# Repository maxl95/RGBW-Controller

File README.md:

# RGBW-Controller
This is a low cost and tasmota compatile RGBW-Controller as an alternative to MagicHome devices.
Everything is untested until now.

# Some specs:
- operating voltage 12V (becaus of the mini360)
- max current per channel (color) 5A in theory 
- fully compatible with [Tasmota](https://github.com/arendst/Tasmota)
- price/piece around 5.60€
- dimensions 20mm x 35mm

# Tasmota template:

# known bugs:
- ~Short circuit between +12V and GND because of a polygon error~

# Pictures:

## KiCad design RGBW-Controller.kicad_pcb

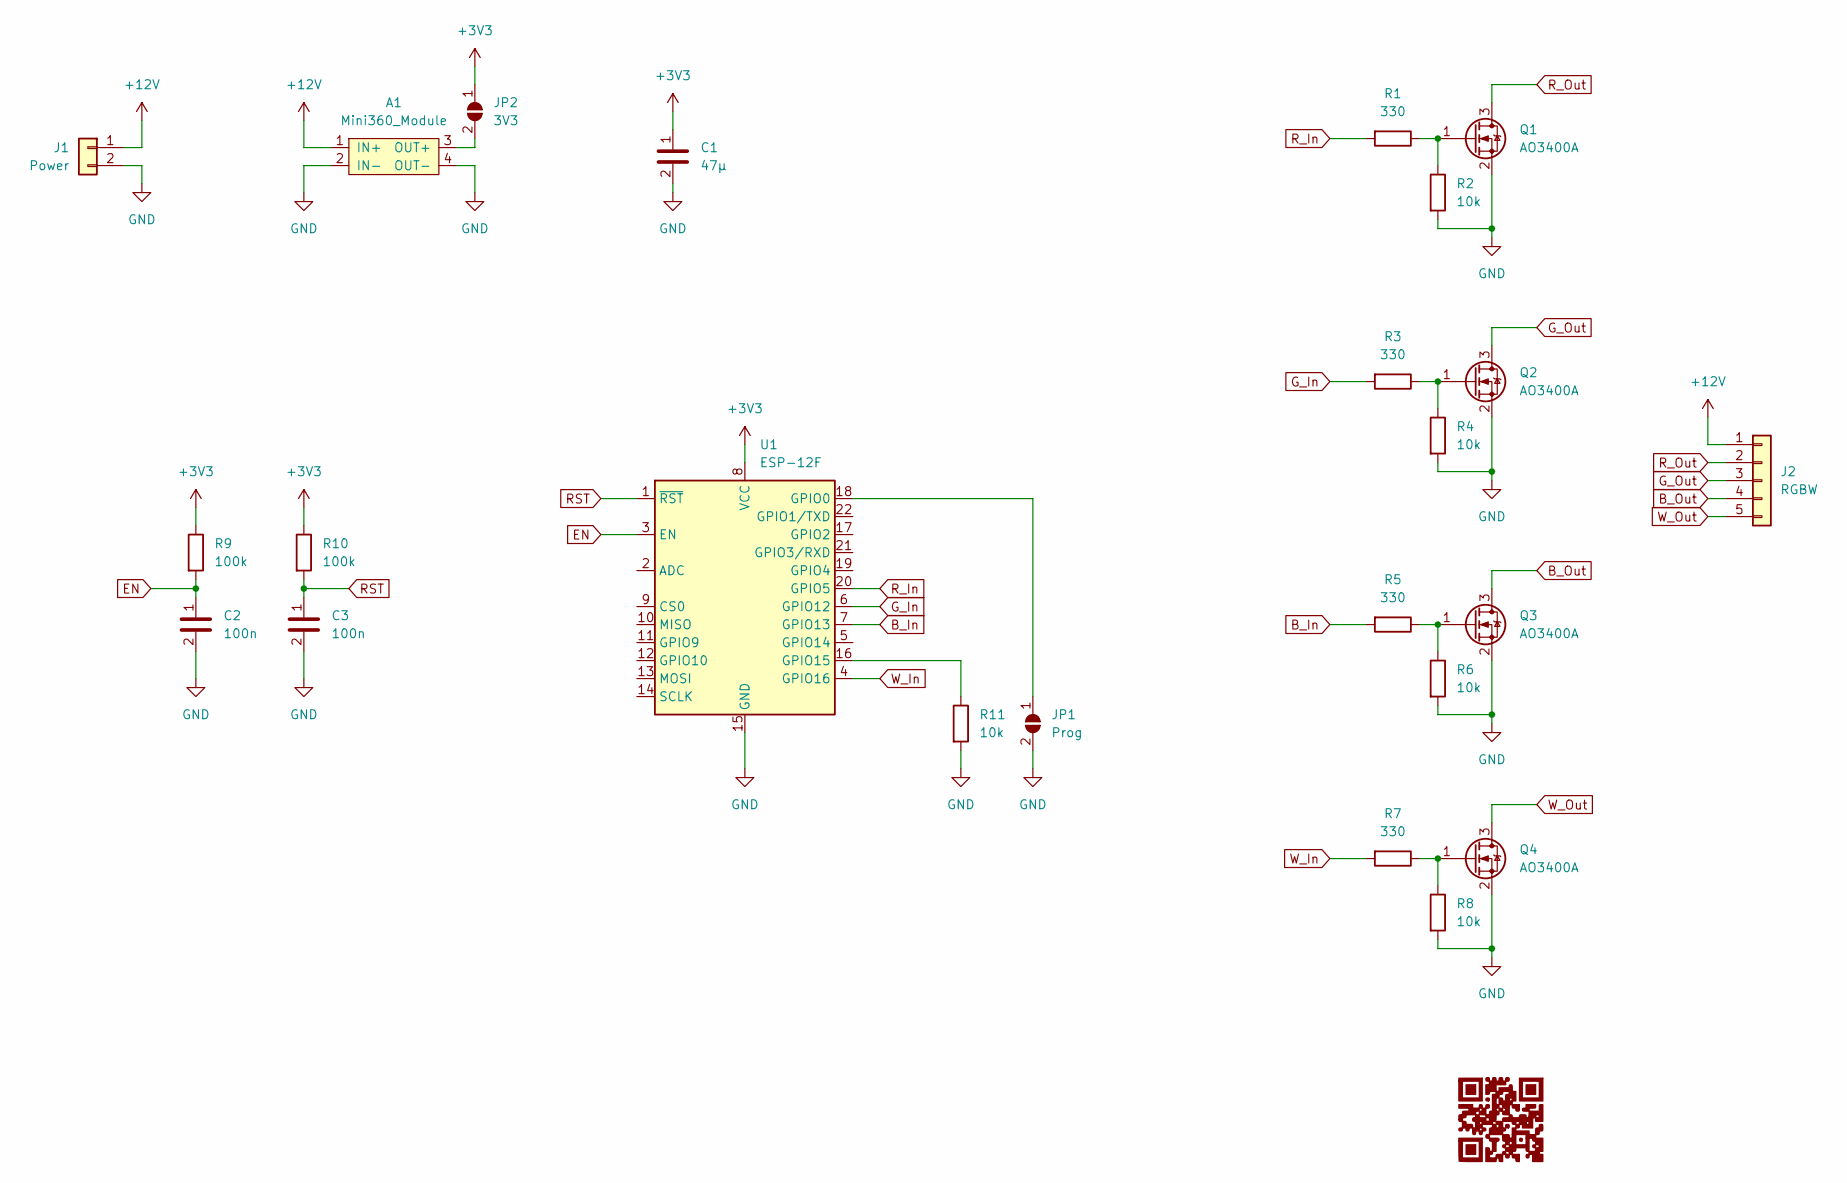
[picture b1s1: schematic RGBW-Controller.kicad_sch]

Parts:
A1: Mini360_Module
C1: 47µ; CP_EIA-3528-12_Kemet-T_Pad1.50x2.35mm_HandSolder
C2, C3: 100n; C_0805_2012Metric_Pad1.18x1.45mm_HandSolder
J1: Power; PinHeader_1x02_P2.54mm_Vertical
J2: RGBW; PinHeader_1x05_P2.54mm_Horizontal
JP1: Prog; SolderJumper-2_P1.3mm_Open_Pad1.0x1.5mm
JP2: 3V3; SolderJumper-2_P1.3mm_Open_Pad1.0x1.5mm
Q1, Q2, Q3, Q4: AO3400A; SOT-23
R1, R3, R5, R7: 330; R_0603_1608Metric
R2, R4, R6, R8: 10k; R_0603_1608Metric
R9, R10: 100k; R_0603_1608Metric_Pad0.98x0.95mm_HandSolder
R11: 10k; R_0603_1608Metric_Pad0.98x0.95mm_HandSolder
U1: ESP-12F; ESP-12E

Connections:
+3V3: C1.1, JP2.1 (A), R9.1, R10.1, U1.8 (VCC)
+12V: A1.1 (IN+), J1.1, J2.1; also elsewhere on the board
B_In: R5.2, U1.7 (GPIO13)
B_Out: J2.4, Q3.3 (D)
EN: C2.1, R9.2, U1.3 (EN)
GND: A1.2 (IN-), A1.4 (OUT-), C1.2, C2.2, C3.2, J1.2, JP1.2 (B), Q1.2 (S), Q2.2 (S), Q3.2 (S), Q4.2 (S), R2.2, R4.2, R6.2, R8.2, R11.2, U1.15 (GND); also elsewhere on the board
G_In: R3.2, U1.6 (GPIO12)
G_Out: J2.3, Q2.3 (D)
unnamed: A1.3 (OUT+), JP2.2 (B)
unnamed: JP1.1 (A), U1.18 (GPIO0)
unnamed: Q1.1 (G), R1.1, R2.1
unnamed: Q2.1 (G), R3.1, R4.1
unnamed: Q3.1 (G), R5.1, R6.1
unnamed: Q4.1 (G), R7.1, R8.1
unnamed: R11.1, U1.16 (GPIO15)
RST: C3.1, R10.2, U1.1 (~RST)
R_In: R1.2, U1.20 (GPIO5)
R_Out: J2.2, Q1.3 (D)
W_In: R7.2, U1.4 (GPIO16)
W_Out: J2.5, Q4.3 (D)

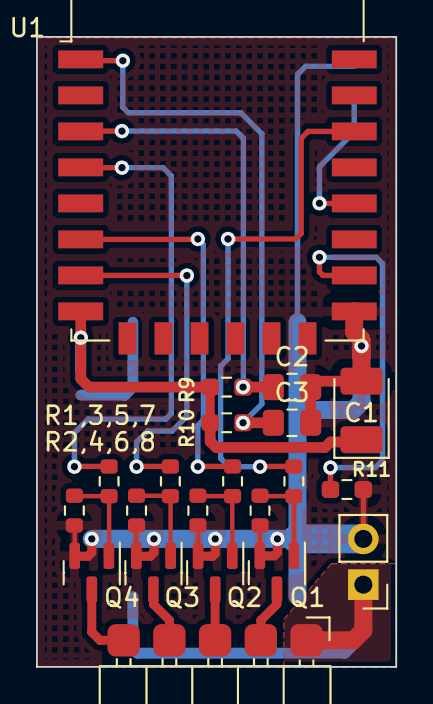
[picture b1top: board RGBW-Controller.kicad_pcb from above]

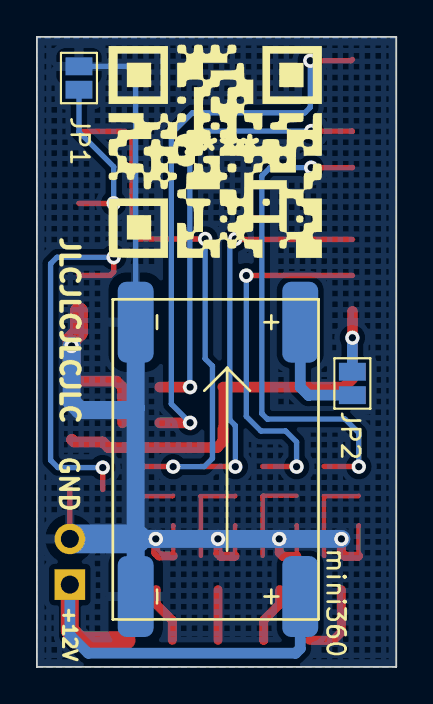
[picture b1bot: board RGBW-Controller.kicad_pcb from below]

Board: 2 copper layers, 20.0 x 35.0 mm, 24 parts (3 on the bottom side), 19 nets.

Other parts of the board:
mini360: Mini360_Module

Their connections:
+12V: mini360.1; also elsewhere on the board
GND: mini360.2, mini360.4; also elsewhere on the board

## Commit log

2020-12-08 Second Commit, applied files from RGB-Controller repo
2020-12-08 edit readme.md
2020-12-08 Edit schematic and layout added pictures
2020-12-08 added collage
2020-12-08 added Gerber files
2020-12-24 discoverd a short circuit between +12V and GND
2020-12-25 removed short circuit between +12V and GND
2020-12-25 Edit readme.md and added updated gerber files
2022-01-31 the whole project in KiCAD, added new pics
2022-02-01 added schematics
2022-02-01 updated footprint of C2 and C3
2022-02-01 Ground plane bug fixed
2022-02-01 edit pictures becuse of ground plane error fix
